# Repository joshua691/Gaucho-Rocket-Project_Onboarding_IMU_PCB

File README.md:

# Rocket Motion Sensing Board — Gaucho Rocket Project

## Overview

This project was developed as part of the onboarding process for Gaucho Rocket Project (GRP). The goal was to design a custom PCB for a rocket motion sensing system capable of collecting inertial measurement data, such as acceleration and angular velocity, and transmitting it wirelessly to other systems.

The board integrates an STM32F446RE microcontroller, an ESP32, an MPU6050 IMU, and an ICM20948 IMU. The STM32 interfaces with both IMUs over I²C and sends the collected sensor data to the ESP32 over UART. This is because the ESP32 is intended to send that data wirelessly to other systems.

Although I had prior experience using KiCad, this was my first project in which I designed most of the schematic and PCB layout independently. It gave me an opportunity to apply what I already knew while developing a deeper understanding of datasheets, circuit implementation, and PCB layout.

## System Architecture

The design consists of four main components:

- **STM32F446RE:** Reads from both IMUs over I²C and forwards sensor data to the ESP32.
- **ESP32:** Receives data from the STM32 over UART and sends that data wirelessly.
- **MPU6050:** Provides accelerometer and gyroscope measurements.
- **ICM20948:** Provides additional inertial measurements.

The board also includes voltage regulation, supporting power circuitry, and connections for programming the STM32 through its Serial Wire Debug (SWD) interface.

## Design Process

The main components were specified by the onboarding assignment, so my focus was on implementing their connections and integrating them into the schematic and PCB layout.

I first used tutorials and the onboarding materials as references for parts of the schematic, particularly the STM32 circuitry. I also consulted the component datasheets to better understand the requirements behind the circuit configurations and the supporting components. Once the schematic was designed, I moved to the PCB layout.

## Schematic

## PCB Design Considerations

### Component Placement and Routing

My main goal during PCB layout was to keep the design as simple and straightforward as possible. I wanted component placement and trace routing as efficient as possible by keeping the traces routes as short and straight as possible and keeping components that have connecting traces as close to each other as possible. This way, the board can be cleaner and more organized to reduce unwanted effects like parasitic inductance and capacitance. During the layout process, I tried to consider how each component would connect to the rest of the circuit when deciding where to place it.

For example, when laying out the STM32's crystal oscillator (Y1), I positioned the supporting capacitor (C10) along the route between the oscillator and the STM32 so that the connections could be routed naturally without unnecessary detours. I applied the same general approach throughout the board, placing related components close together, keeping the STM32 and ESP32 positioned with their UART connections in mind, and minimizing vias between PCB layers.

I also considered power distribution while arranging components and routing traces, including the placement of voltage regulators and the trace widths used for different power nets. I placed the majority of the capacitors close to their corresponding pins on the microcontrollers, IMUs, or regulators to help reduce parasitic inductance in the paths and support stable power delivery.

Overall, I approached the layout largely considering component placement and routing, aiming for a compact, organized board where the connections were as direct as possible and the supporting circuitry was positioned around the components it served.

### Firmware Programming Access

I included access to the STM32's SWDIO and SWCLK pins by adding connector pins that connects to them to support firmware flashing and debugging through the Serial Wire Debug interface, provides a way to program the microcontroller.

## Final PCB Layout

## Project Status and Future Work

The schematic and PCB layout were completed in KiCad, but the board was not manufactured or tested. Its electrical performance and functionality have therefore not been validated on physical hardware.

Future work would include reviewing the design against component datasheets and PCB design rules, manufacturing the board, and testing the power supplies, sensor interfaces, UART communication, wireless data path, and overall functionality of the PCB.

## Lessons Learned

This process helped me connect schematic-level decisions to the physical constraints of PCB design. Since this was the first PCB I designed primarily myself, I gained experience balancing component placement and routing, considering power distribution and decoupling, and providing programming access for firmware development.

It also gave me a better appreciation for how initial component placement affects routing complexity and how datasheets can guide hardware implementation and what the overarching design of a PCB would be since datasheets tell exactly what the supporting circuitry for a component is, what the power requirements are, and what the components are capable of.

## Tools and Interfaces

- **KiCad:** Schematic capture and PCB layout
- **I²C:** Communication between the STM32 and IMUs
- **UART:** Communication between the STM32 and ESP32
- **SWD:** STM32 firmware programming and debugging

## 3D PCB View

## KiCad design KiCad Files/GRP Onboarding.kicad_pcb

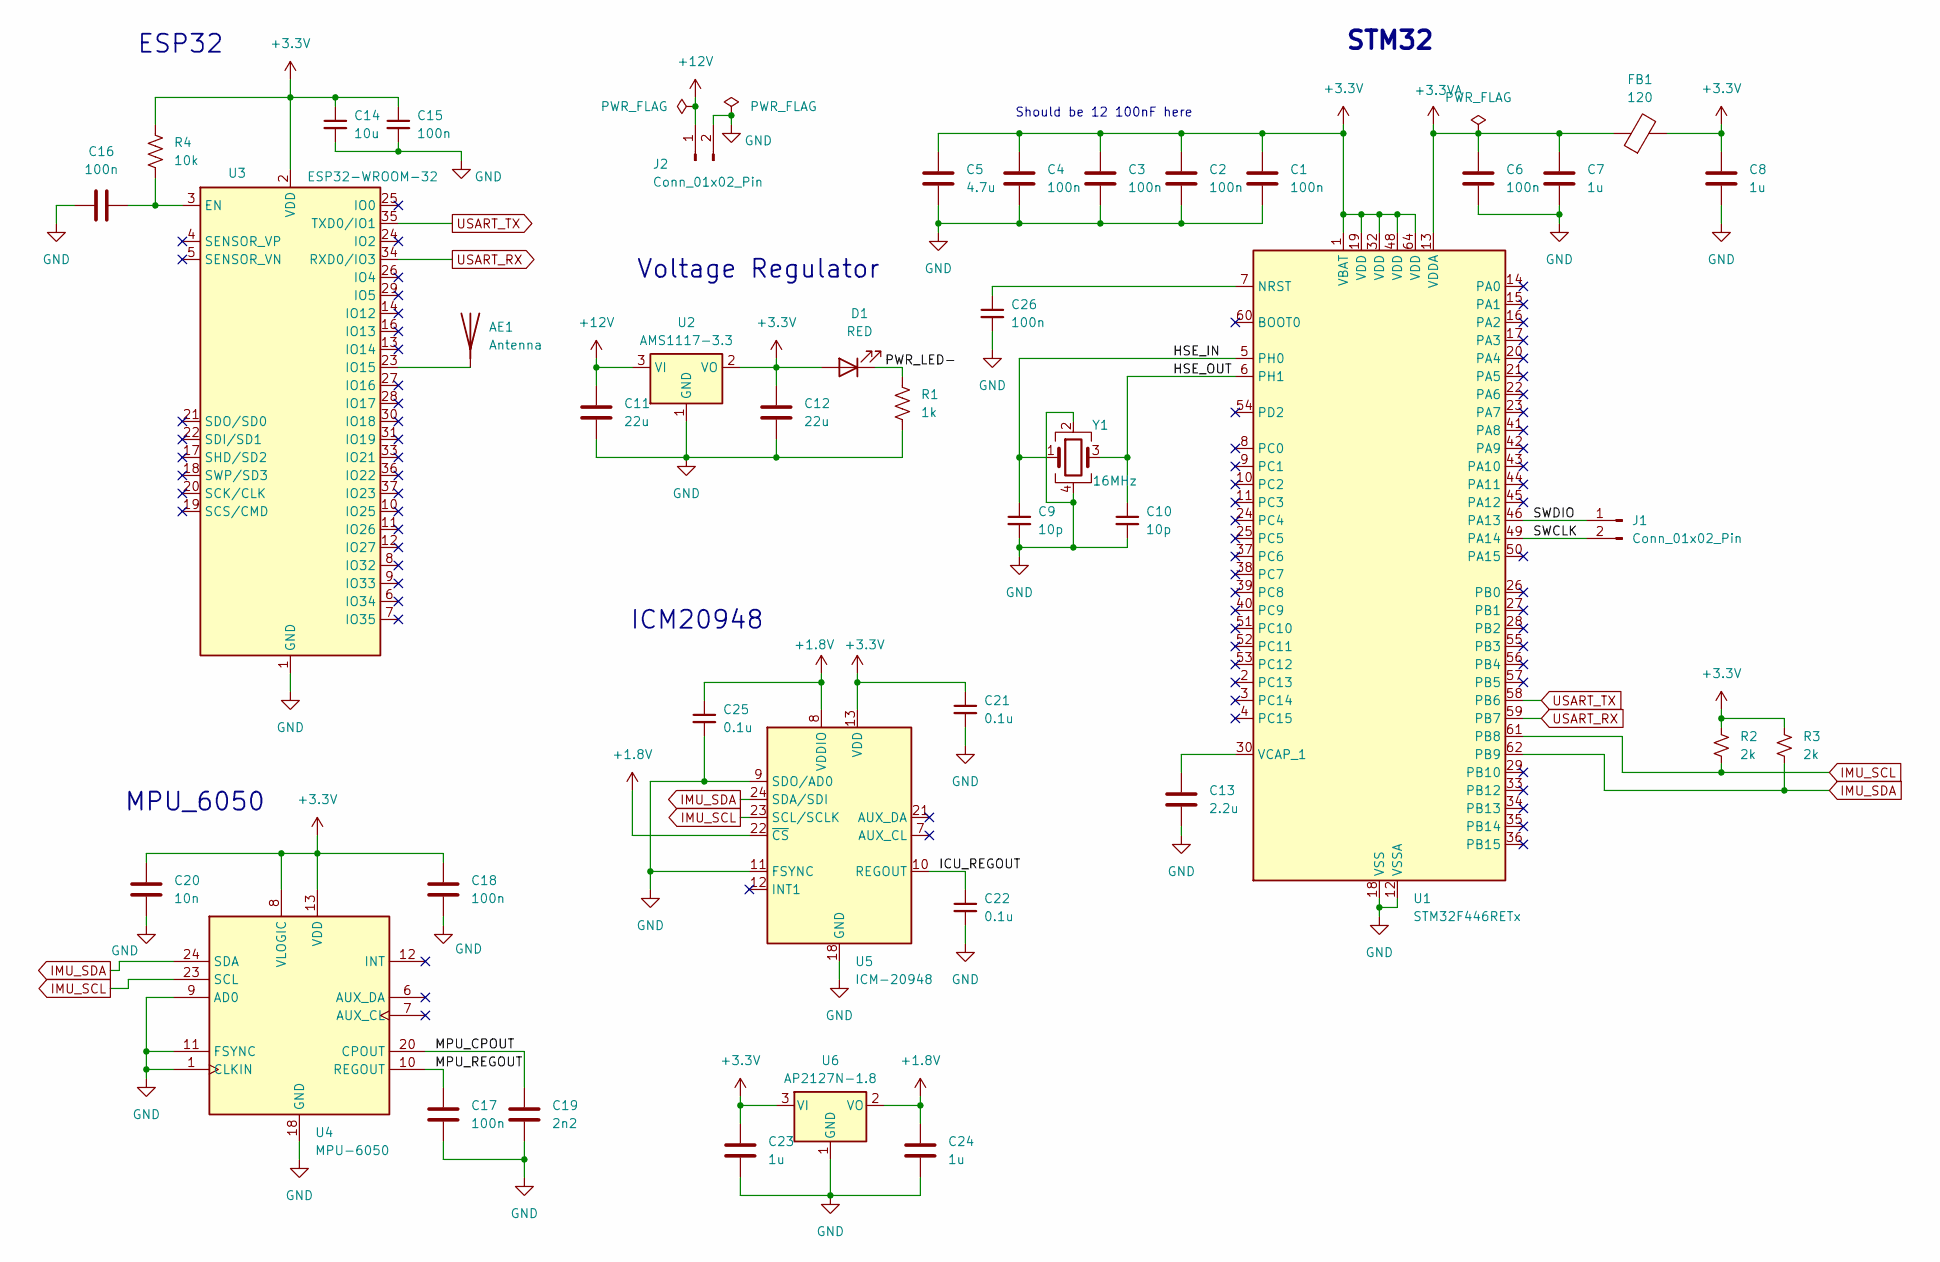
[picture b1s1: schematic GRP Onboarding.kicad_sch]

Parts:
AE1: Antenna; AVX_M620720
C1, C2, C3, C4, C6, C26: 100n; C_0402_1005Metric
C5: 4.7u; C_0603_1608Metric
C7, C8, C23, C24: 1u; C_0402_1005Metric
C9, C10: 10p; C_0402_1005Metric
C11, C12: 22u; C_0805_2012Metric
C13: 2.2u; C_0603_1608Metric
C14: 10u; C_0603_1608Metric
C15, C16, C17, C18: 100n; C_01005_0402Metric
C19: 2n2; C_01005_0402Metric
C20: 10n; C_01005_0402Metric
C21, C22, C25: 0.1u; C_01005_0402Metric
D1: RED; LED_0603_1608Metric
FB1: 120; L_0603_1608Metric
J1, J2: Conn_01x02_Pin; PinHeader_1x02_P2.54mm_Vertical
R1: 1k; R_0402_1005Metric
R2, R3: 2k; R_0402_1005Metric
R4: 10k; R_0402_1005Metric
U1: STM32F446RETx; LQFP-64_10x10mm_P0.5mm
U2: AMS1117-3.3; SOT-223-3_TabPin2
U3: ESP32-WROOM-32
U4: MPU-6050; InvenSense_QFN-24_4x4mm_P0.5mm
U5: ICM-20948; InvenSense_QFN-24_3x3mm_P0.4mm
U6: AP2127N-1.8; SOT-23
Y1: 16MHz; Crystal_SMD_3225-4Pin_3.2x2.5mm

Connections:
+1.8V: C24.1, C25.1, U5.8 (VDDIO), U5.22 (~CS), U6.2 (VO)
+3.3V: C1.1, C2.1, C3.1, C4.1, C5.1, C8.1, C12.1, C14.1, C15.1, C18.1, C20.1, C21.1, C23.1, D1.2 (A), FB1.2, R2.1, R3.1, R4.1, U1.1 (VBAT), U1.19 (VDD), U1.32 (VDD), U1.48 (VDD), U1.64 (VDD), U2.2 (VO), U3.2 (VDD), U4.8 (VLOGIC), U4.13 (VDD), U5.13 (VDD), U6.3 (VI)
+3.3VA: C6.1, C7.1, FB1.1, U1.13 (VDDA)
+12V: C11.1, J2.1, U2.3 (VI)
/HSE_IN: C9.1, U1.5 (PH0), Y1.1
/HSE_OUT: C10.1, U1.6 (PH1), Y1.3
/ICU_REGOUT: C22.1, U5.10 (REGOUT)
/MPU_CPOUT: C19.1, U4.20 (CPOUT)
/MPU_REGOUT: C17.1, U4.10 (REGOUT)
/PWR_LED-: D1.1 (K), R1.1
/SWCLK: J1.2, U1.49 (PA14)
/SWDIO: J1.1, U1.46 (PA13)
GND: C1.2, C2.2, C3.2, C4.2, C5.2, C6.2, C7.2, C8.2, C9.2, C10.2, C11.2, C12.2, C13.2, C14.2, C15.2, C16.1, C17.2, C18.2, C19.2, C20.2, C21.2, C22.2, C23.2, C24.2, C25.2, C26.2, J2.2, R1.2, U1.12 (VSSA), U1.18 (VSS), U1.31 (VSS), U1.47 (VSS), U1.63 (VSS), U2.1 (GND), U3.1 (GND), U3.15 (GND), U3.38 (GND), U3.39 (GND), U4.1 (CLKIN), U4.9 (AD0), U4.11 (FSYNC), U4.18 (GND), U5.9 (SDO/AD0), U5.11 (FSYNC), U5.18 (GND), U5.20 (GND), U6.1 (GND), Y1.2, Y1.4
IMU_SCL: R2.2, U1.61 (PB8), U4.23 (SCL), U5.23 (SCL/SCLK)
IMU_SDA: R3.2, U1.62 (PB9), U4.24 (SDA), U5.24 (SDA/SDI)
unnamed: AE1.1 (A), U3.23 (IO15)
unnamed: C26.1, U1.7 (NRST)
unnamed: C13.1, U1.30 (VCAP_1)
unnamed: C16.2, R4.2, U3.3 (EN)
USART_RX: U1.59 (PB7), U3.34 (RXD0/IO3)
USART_TX: U1.58 (PB6), U3.35 (TXD0/IO1)

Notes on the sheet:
ICM20948
Should be 12 100nF here
MPU_6050
Voltage Regulator
ESP32
STM32

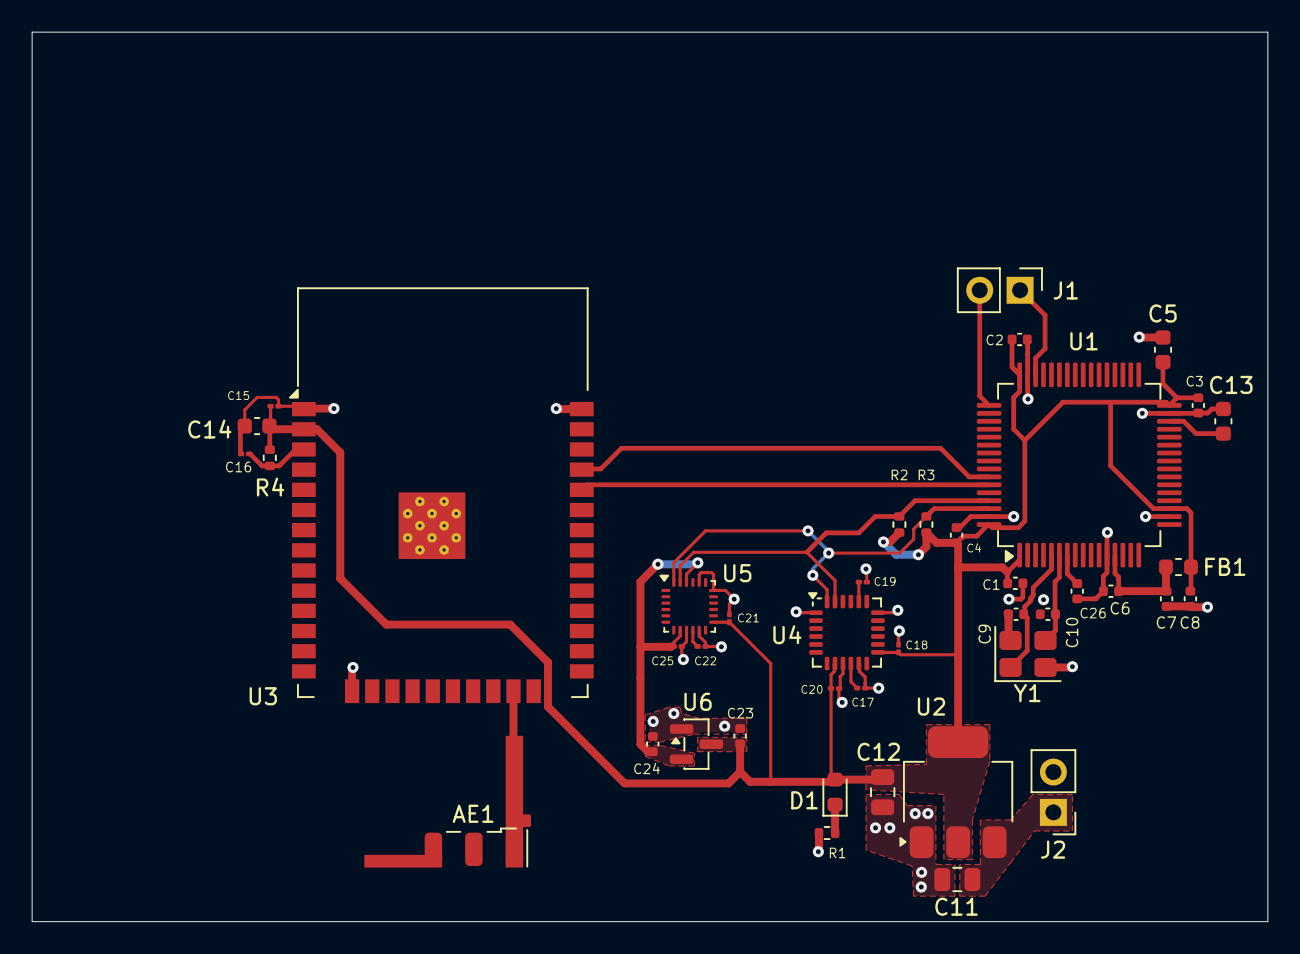
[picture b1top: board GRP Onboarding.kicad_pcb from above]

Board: 2 copper layers, 77.8 x 56.0 mm, 42 parts (0 on the bottom side), 21 nets.
